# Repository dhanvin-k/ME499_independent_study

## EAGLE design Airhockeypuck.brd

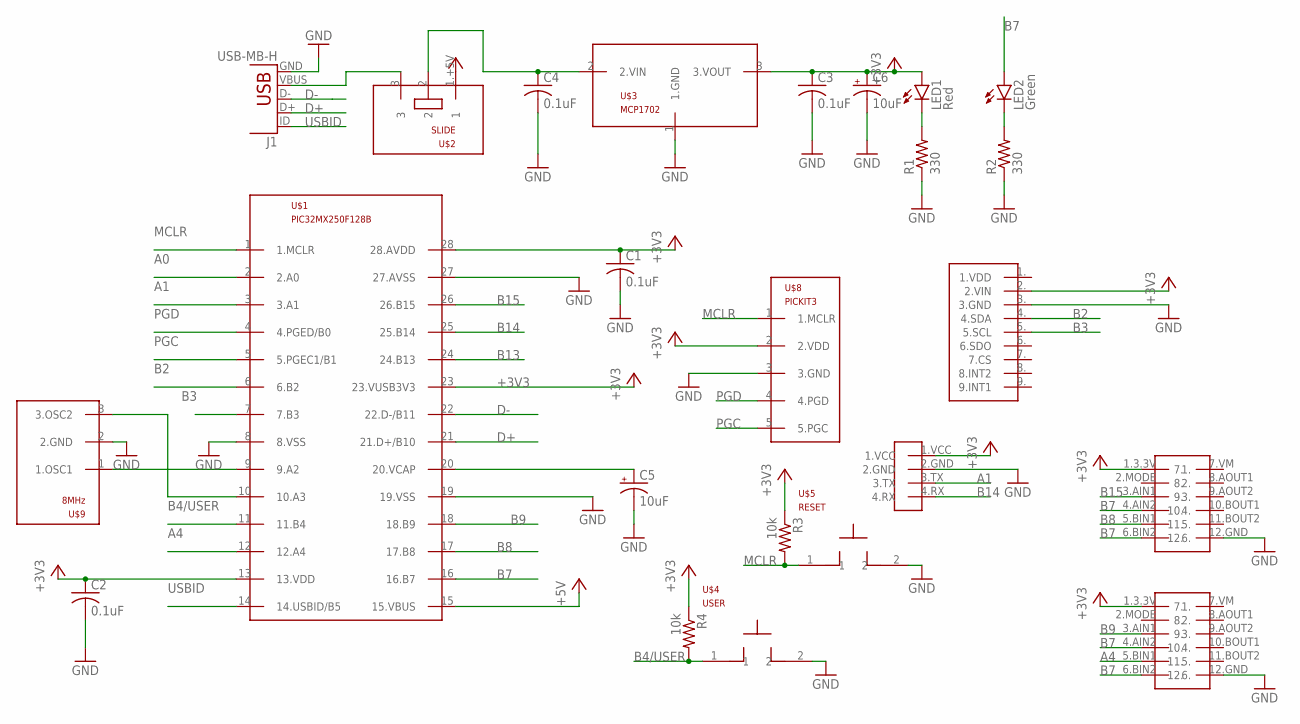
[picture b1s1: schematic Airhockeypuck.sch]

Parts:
C1, C2, C3, C4: 0.1uF; C025-025X050
C5, C6: 10uF; B45181B
J1: USB-MB-H
LED1: Red; LED3MM
LED2: Green; LED3MM
R1, R2: 330; 0207/10
R3, R4: 10k; 0207/10
U$1: PIC32MX250F128B; DIL28-3
U$2: SLIDE
U$3: MCP1702; TO92
U$4: USER; PB
U$5: RESET; PB
U$6, U$7: DRV8835
U$8: PICKIT3; 1X05
U$9: 8MHz; OSC
U$10: IMU
U$11: HC-08

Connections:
+3V3: C1.1, C2.1, C3.1, C6.+, LED1.A, R3.1, R4.1, U$1.13 (13.VDD), U$1.23 (23.VUSB3V3), U$1.28 (28.AVDD), U$3.3 (3.VOUT), U$6.1.3.3V (1.), U$7.1.3.3V (1.), U$8.2 (2.VDD), U$10.2. (2.VIN)
+5V: U$1.15 (15.VBUS), U$2.1.+5V (1)
A0: U$1.2 (2.A0)
A1: U$1.3 (3.A1), U$11.3.TX
A4: U$1.12 (12.A4), U$7.5.BIN1 (5.)
B2: U$1.6 (6.B2), U$10.4. (4.SDA)
B3: U$1.7 (7.B3), U$10.5. (5.SCL)
B4/USER: R4.2, U$1.11 (11.B4), U$4.1
B7: LED2.A, U$1.16 (16.B7), U$6.4.AIN2 (4.), U$6.6.BIN2 (6.), U$7.4.AIN2 (4.), U$7.6.BIN2 (6.)
B8: U$1.17 (17.B8), U$6.5.BIN1 (5.)
B9: U$1.18 (18.B9), U$7.3.AIN1 (3.)
B13: U$1.24 (24.B13)
B14: U$1.25 (25.B14), U$11.4.RX
B15: U$1.26 (26.B15), U$6.3.AIN1 (3.)
D+: J1.D+, U$1.21 (21.D+/B10)
D-: J1.D-, U$1.22 (22.D-/B11)
GND: C1.2, C2.2, C3.2, C4.2, C5.-, C6.-, J1.GND, R1.1, R2.1, U$1.8 (8.VSS), U$1.19 (19.VSS), U$1.27 (27.AVSS), U$3.1 (1.GND), U$4.2, U$5.2, U$6.12.GND (12.), U$7.12.GND (12.), U$8.3 (3.GND), U$9.2 (2.GND), U$10.3. (3.GND), U$11.2.GND
MCLR: R3.2, U$1.1 (1.MCLR), U$5.1, U$8.1 (1.MCLR)
unnamed: J1.VBUS, U$2.3
unnamed: U$1.9 (9.A2), U$9.1 (1.OSC1)
unnamed: LED2.K (C), R2.2
unnamed: LED1.K (C), R1.2
unnamed: U$1.10 (10.A3), U$9.3 (3.OSC2)
unnamed: C5.+, U$1.20 (20.VCAP)
unnamed: C4.1, U$2.2, U$3.2 (2.VIN)
PGC: U$1.5 (5.PGEC1/B1), U$8.5 (5.PGC)
PGD: U$1.4 (4.PGED/B0), U$8.4 (4.PGD)
USBID: J1.ID, U$1.14 (14.USBID/B5)

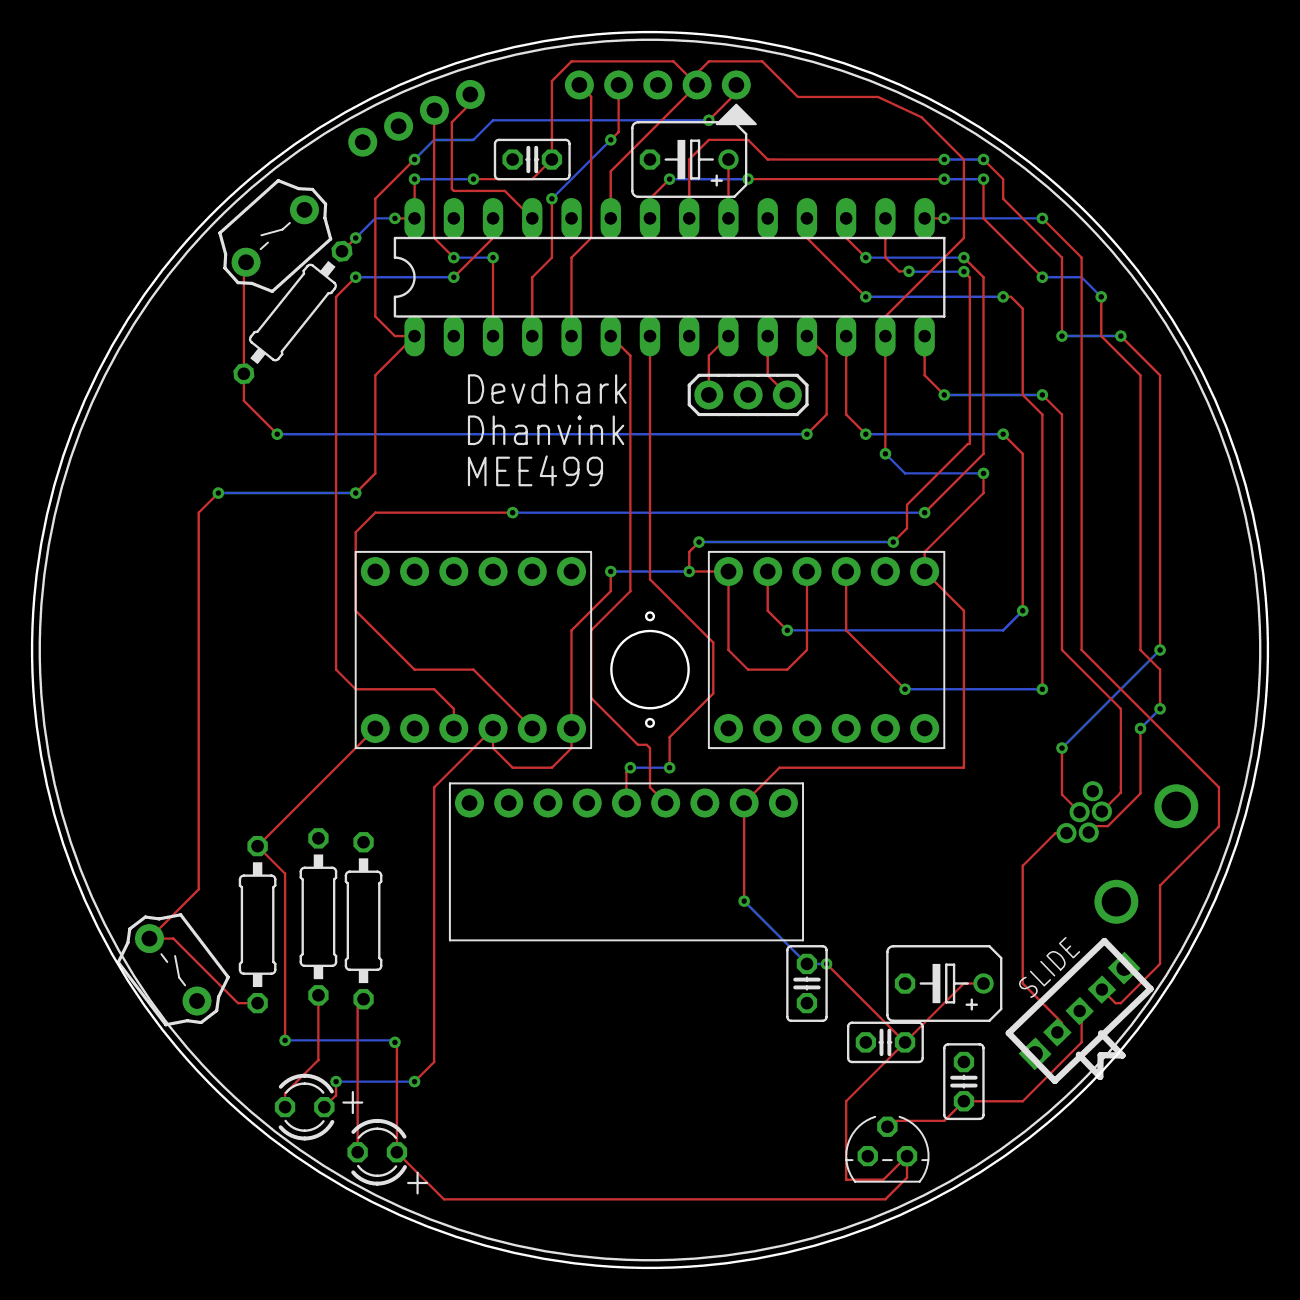
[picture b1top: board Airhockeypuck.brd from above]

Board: 2 copper layers, 80.0 x 80.0 mm, 24 parts (0 on the bottom side), 26 nets.

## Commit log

2019-10-04 added ME433 library file
2019-10-10 started PCB design
2019-10-10 arranged all components on the board
2019-10-11 minor edits
2019-10-12 Created IMU part and added into PCB design
2019-10-14 created DRV8835 device
    added to PCB design
2019-10-14 created HC-08 pins and added
2019-10-21 minor edits to PCB
2019-11-03 completed connections
2019-11-03 error-checking passed
2019-11-03 generated gerber files for manufacturing
2019-11-11 Changed device DRV8835
